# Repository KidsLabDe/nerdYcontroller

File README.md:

# Innovative Lernplatine mit Raspberry Pi Pico für angehende Programmierer

Diese benutzerfreundliche Platine ist speziell darauf ausgelegt, einen Raspberry Pi Pico aufzunehmen, und bietet eine interaktive Plattform, um die Grundlagen der Programmierung und Elektronik spielerisch zu erlernen.

**Hauptmerkmale:**

- **Vielseitiger Raspberry Pi Pico-Sockel:** Im Herzen der Platine befindet sich ein dedizierter Sockel, der perfekt für den Raspberry Pi Pico geeignet ist. Dies ermöglicht eine einfache Integration und eine robuste Verbindung.

- **Farbenfrohe LED-Anzeige:** Ausgestattet mit vier leuchtenden LEDs in verschiedenen Farben, bietet unsere Platine eine visuelle Rückmeldung für Programmierprojekte. Diese LEDs können für eine Vielzahl von Projekten programmiert werden, von einfachen Blinkmustern bis hin zu komplexeren Sequenzen.

- **Integrierter Neigungssensor:** Mit dem eingebauten Neigungssensor können Nutzer Bewegung und Ausrichtung in ihre Projekte einbeziehen. Dieser Sensor eröffnet spannende Möglichkeiten für interaktive Spiele und Experimente.

- **Kompakter Lautsprecher:** Ein kleiner, aber leistungsstarker Lautsprecher ermöglicht es, akustische Elemente in Projekte zu integrieren. Von einfachen Tonsignalen bis hin zu komplexen Melodien können die Nutzer ihre Kreativität voll ausleben.

- **Touch-Sensoren:** Die Platine verfügt über empfindliche Touch-Sensoren, die eine neue Dimension der Interaktivität bieten. Diese können für eine Vielzahl von Anwendungen genutzt werden, von Steuerelementen für Spiele bis hin zu kreativen musikalischen Experimenten.

- **Ideal für DIY-Gamecontroller:** Diese Platine ist nicht nur ein Lernwerkzeug, sondern auch eine Grundlage für den Bau eigener Gamecontroller. Nutzer können die vorhandenen Sensoren und Ausgänge verwenden, um einzigartige und individuelle Spieleerlebnisse zu schaffen.

**Anwendungsbereiche:**

Diese Platine ist ideal für Bildungseinrichtungen, Maker und alle, die einen praktischen und unterhaltsamen Einstieg in die Welt des Programmierens suchen. Sie bietet eine solide Grundlage für Projekte in den Bereichen Robotik, Spieleentwicklung und interaktive Kunst.

# Zusammenbau und erster Start

**Merke: Das Zusammenbauen ist nicht schwer - sie beim Löten zu brennen schmerzt dagegen sehr!** 

Daher immer auf die Finger obacht geben und den Lötkolben sicher ablegen!

## 1. Alles was du brauchst!

- Lötkolben, Lötzinn etc.
- 2 "Header" - die nutzen wir, um den Pico richtig auf der Platine zu platzieren. Im Notfall gehen auch 2 Büroklammern...
- einen [Raspberry Pico](https://www.berrybase.de/raspberry-pi-pico-rp2040-mikrocontroller-board) (oder [Pico W](https://www.berrybase.de/raspberry-pi-pico-w-rp2040-wlan-mikrocontroller-board))

## 2. Richtig platzieren

Lege den Pico auf die Platine. 

** Achtung - der USB-Stecker muss oben sein! **

Bitte achte auch darauf, dass der Pico nicht verschoben ist.

## 3. Let's Löt!

(Danke an Adafruit!)

- Lötkolben aufheizen
- Lötstelle mit Spitze berühren - am besten vor der Seite
- Etwas lötzinn zugeben
- 2-3 Sekunden warten!
- Jetzt etwas mehr Lötzinn von oben zugeben, es schmilzt an der Platine

Zuerst 2-3 Pins anlöten, zum Beispiel links oben und rechts unten - dann ist der Pico fest und du kannst die Header entfernen.

So sieht es aus, wenn alles fertig ist!

## 4. Anschließen und Software aufspielen!

- Stecke den Pico mit einem Micro-USB Kabel am Computer an.
- Wenn er neu ist, sollte er sofort wie ein USB-Stick auftauchen
- Wenn nicht, halte beim Anstecken die kleine weiße Taste "BOOTSEL" gedrückt.

So sieht das auf dem Mac aus:

(Bei Windows ein bisschen anders...)

Jetzt fehlt nur noch die "Firmware" - das ist die Basis-Software, damit der Pico Python sprechen kann: zusätzlich habe ich noch einen Beispiel-Python-Code drauf gemacht, dass es blinkt etc.

1. Lade diese Datei runter: https://github.com/KidsLabDe/PicoKrokoBirne/blob/main/firmware/PicoKrokoBirne.uf2
2. Kopiere sie auf die Pico im Finder / Explorer. Das geht meistens per Drag&Drop
3. Fertig!

Die PicoKrokoBirne sollte jetzt fröhlich bunt drauf losblinken!

## Anpassen und los programmieren!

Der Pico erscheint nun wiederum als USB-Laufwerk, diesmal heißt er "CIRCUITPY".
Dort findest du die Datei "code.py" - da drin passiert die Magie!

Als Editor empfehle ich dir den Mu-Editor: https://codewith.mu

Viel Spaß!

# Kontaktdaten

Du hast die Glühbirne als Visitenkarte bekommen? Sehr gut! 

Meine Kontaktdaten:

- Gregor Walter
- [gregor@kidslab.de](mailto:gregor@kidslab.de
- Telefon / WhatsApp: 0821-99951920 
- Mehr Infos über das gemeinnützige [KidsLab](https://kidslab.de) 

Ich freue mich auf deinen Anruf / eMail / Nachricht 🤖

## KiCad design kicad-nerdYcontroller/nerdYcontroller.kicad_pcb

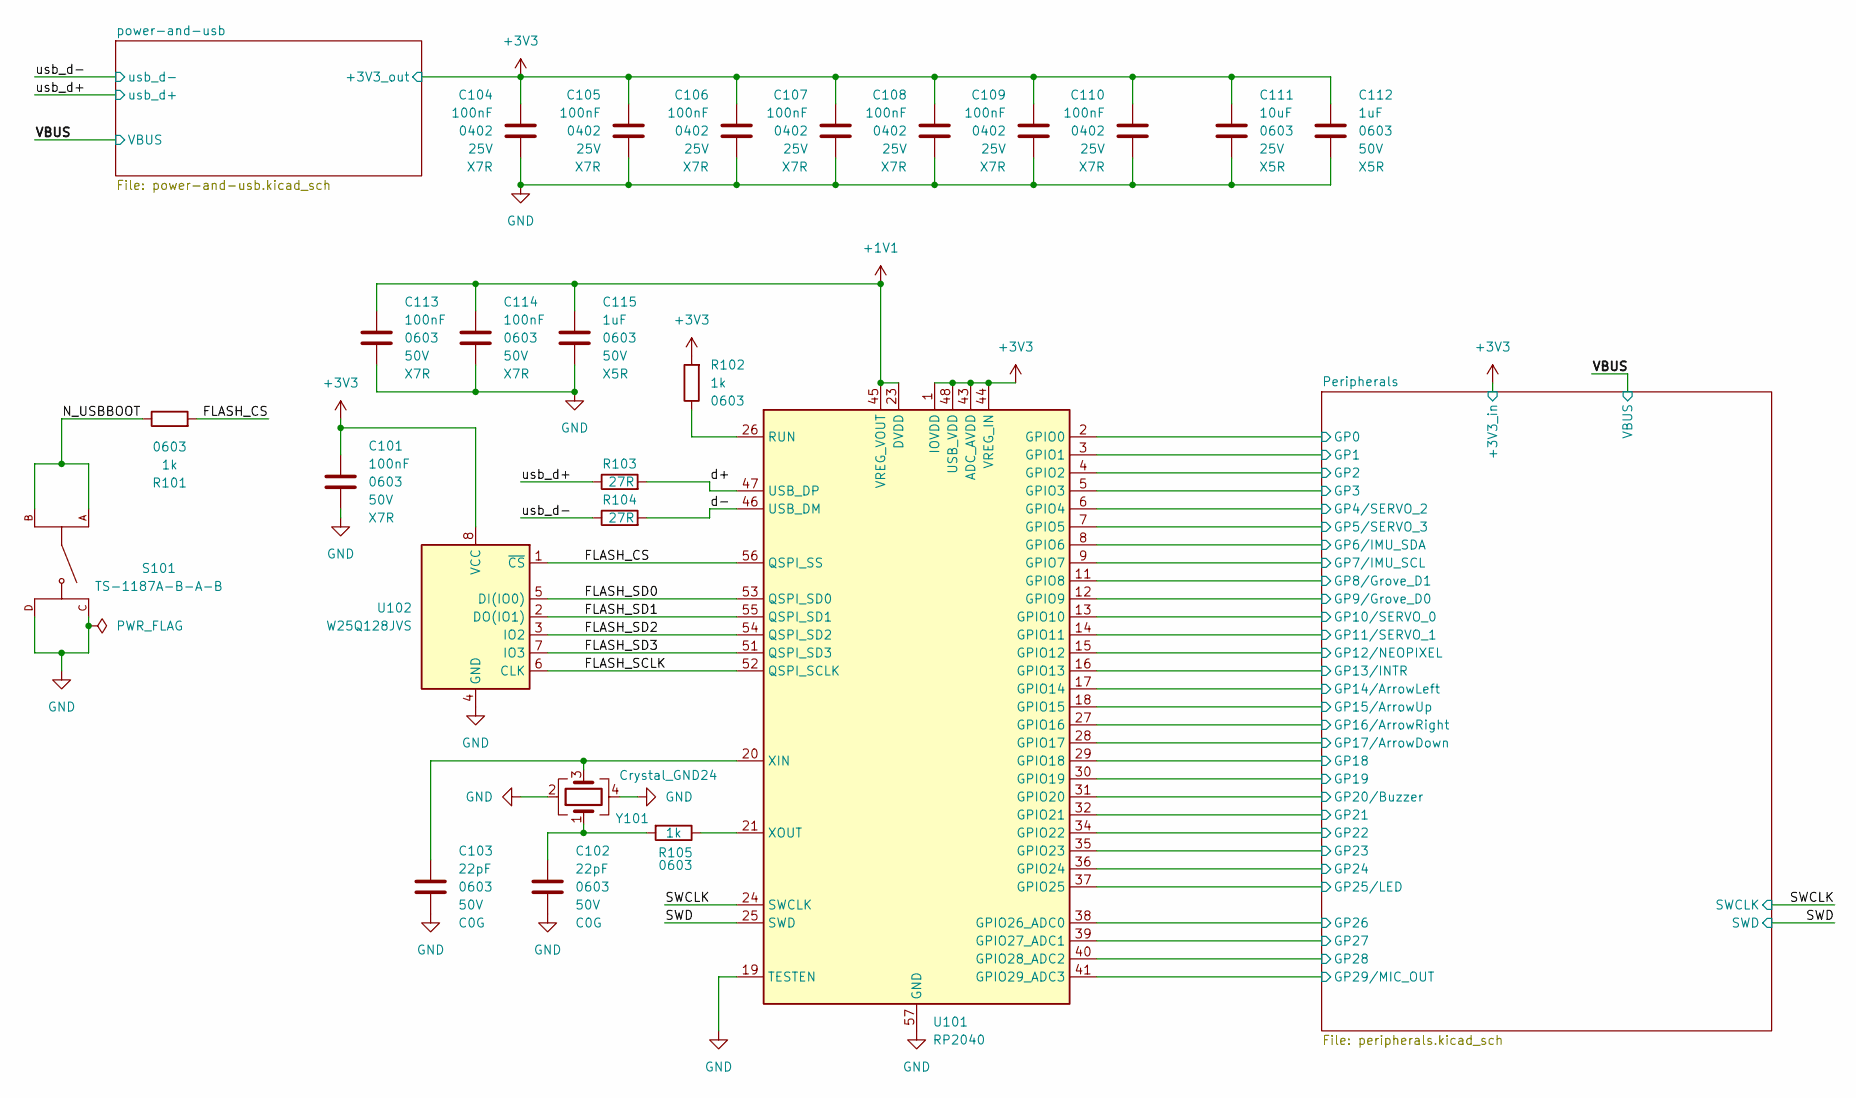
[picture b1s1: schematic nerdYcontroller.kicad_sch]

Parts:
C101, C113, C114: 100nF; C_0603_1608Metric; Voltage Rating 50V; LCSC Part # C14663
C102, C103: 22pF; C_0603_1608Metric; Voltage Rating 50V; LCSC Part # C1653
C104, C105, C106, C107, C108, C109, C110: 100nF; C_0402_1005Metric; Voltage Rating 25V; LCSC Part # C56392
C111: 10uF; C_0603_1608Metric; Voltage Rating 25V; LCSC Part # C96446
C112, C115: 1uF; C_0603_1608Metric; Voltage Rating 50V; LCSC Part # C15849
R101, R102, R105: 1k; R_0603_1608Metric; LCSC Part # C21190
R103, R104: 27R; R_0603_1608Metric; LCSC Part # C25190
S101: TS-1187A-B-A-B; SW_TS-1187A-B-A-B; LCSC Part # C318884
U101: RP2040; QFN-56-1EP_7x7mm_P0.4mm_EP3.2x3.2mm
U102: W25Q128JVS; SOIC-8_5.23x5.23mm_P1.27mm; LCSC Part # C97521
Y101: Crystal_GND24; Crystal_SMD_3225-4Pin_3.2x2.5mm; LCSC Part # C9002

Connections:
+1V1: C113.1, C114.1, C115.1, U101.23 (DVDD), U101.45 (VREG_VOUT), U101.50 (DVDD)
+3V3: C101.1, C104.2, C105.2, C106.2, C107.2, C108.2, C109.2, C110.2, C111.1, C112.1, R102.2, U101.1 (IOVDD), U101.10 (IOVDD), U101.22 (IOVDD), U101.33 (IOVDD), U101.42 (IOVDD), U101.43 (ADC_AVDD), U101.44 (VREG_IN), U101.48 (USB_VDD), U101.49 (IOVDD), U102.8 (VCC); also elsewhere on the board
/FLASH_CS: R101.2, U101.56 (QSPI_SS), U102.1 (~CS)
/FLASH_SCLK: U101.52 (QSPI_SCLK), U102.6 (CLK)
/FLASH_SD0: U101.53 (QSPI_SD0), U102.5 (DI(IO0))
/FLASH_SD1: U101.55 (QSPI_SD1), U102.2 (DO(IO1))
/FLASH_SD2: U101.54 (QSPI_SD2), U102.3 (IO2)
/FLASH_SD3: U101.51 (QSPI_SD3), U102.7 (IO3)
/N_USBBOOT: R101.1, S101.A, S101.B
/Peripherals/GP0: U101.2 (GPIO0); also elsewhere on the board
/Peripherals/GP1: U101.3 (GPIO1); also elsewhere on the board
/Peripherals/GP2: U101.4 (GPIO2); also elsewhere on the board
/Peripherals/GP3: U101.5 (GPIO3); also elsewhere on the board
/Peripherals/GP4/SERVO_2: U101.6 (GPIO4); also elsewhere on the board
/Peripherals/GP5/SERVO_3: U101.7 (GPIO5); also elsewhere on the board
/Peripherals/GP6/IMU_SDA: U101.8 (GPIO6); also elsewhere on the board
/Peripherals/GP7/IMU_SCL: U101.9 (GPIO7); also elsewhere on the board
/Peripherals/GP8/Grove_D1: U101.11 (GPIO8); also elsewhere on the board
/Peripherals/GP9/Grove_D0: U101.12 (GPIO9); also elsewhere on the board
/Peripherals/GP10/SERVO_0: U101.13 (GPIO10); also elsewhere on the board
/Peripherals/GP11/SERVO_1: U101.14 (GPIO11); also elsewhere on the board
/Peripherals/GP12/NEOPIXEL: U101.15 (GPIO12); also elsewhere on the board
/Peripherals/GP13/INTR: U101.16 (GPIO13); also elsewhere on the board
/Peripherals/GP14/ArrowLeft: U101.17 (GPIO14); also elsewhere on the board
/Peripherals/GP15/ArrowUp: U101.18 (GPIO15); also elsewhere on the board
/Peripherals/GP16/ArrowRight: U101.27 (GPIO16); also elsewhere on the board
/Peripherals/GP17/ArrowDown: U101.28 (GPIO17); also elsewhere on the board
/Peripherals/GP18: U101.29 (GPIO18); also elsewhere on the board
/Peripherals/GP19: U101.30 (GPIO19); also elsewhere on the board
/Peripherals/GP20/Buzzer: U101.31 (GPIO20); also elsewhere on the board
/Peripherals/GP21: U101.32 (GPIO21); also elsewhere on the board
/Peripherals/GP22: U101.34 (GPIO22); also elsewhere on the board
/Peripherals/GP23: U101.35 (GPIO23); also elsewhere on the board
/Peripherals/GP24: U101.36 (GPIO24); also elsewhere on the board
/Peripherals/GP25/LED: U101.37 (GPIO25); also elsewhere on the board
/Peripherals/GP26: U101.38 (GPIO26_ADC0); also elsewhere on the board
/Peripherals/GP27: U101.39 (GPIO27_ADC1); also elsewhere on the board
/Peripherals/GP28: U101.40 (GPIO28_ADC2); also elsewhere on the board
/Peripherals/GP29/MIC_OUT: U101.41 (GPIO29_ADC3); also elsewhere on the board
/SWCLK: U101.24 (SWCLK); also elsewhere on the board
/SWD: U101.25 (SWD); also elsewhere on the board
/d+: R103.2, U101.47 (USB_DP)
/d-: R104.2, U101.46 (USB_DM)
/usb_d+: R103.1; also elsewhere on the board
/usb_d-: R104.1; also elsewhere on the board
GND: C101.2, C102.2, C103.2, C104.1, C105.1, C106.1, C107.1, C108.1, C109.1, C110.1, C111.2, C112.2, C113.2, C114.2, C115.2, S101.C, S101.D, U101.19 (TESTEN), U101.57 (GND), U102.4 (GND), Y101.2, Y101.4; also elsewhere on the board
unnamed: C102.1, R105.2, Y101.1
unnamed: R102.1, U101.26 (RUN)
unnamed: C103.1, U101.20 (XIN), Y101.3
unnamed: R105.1, U101.21 (XOUT)

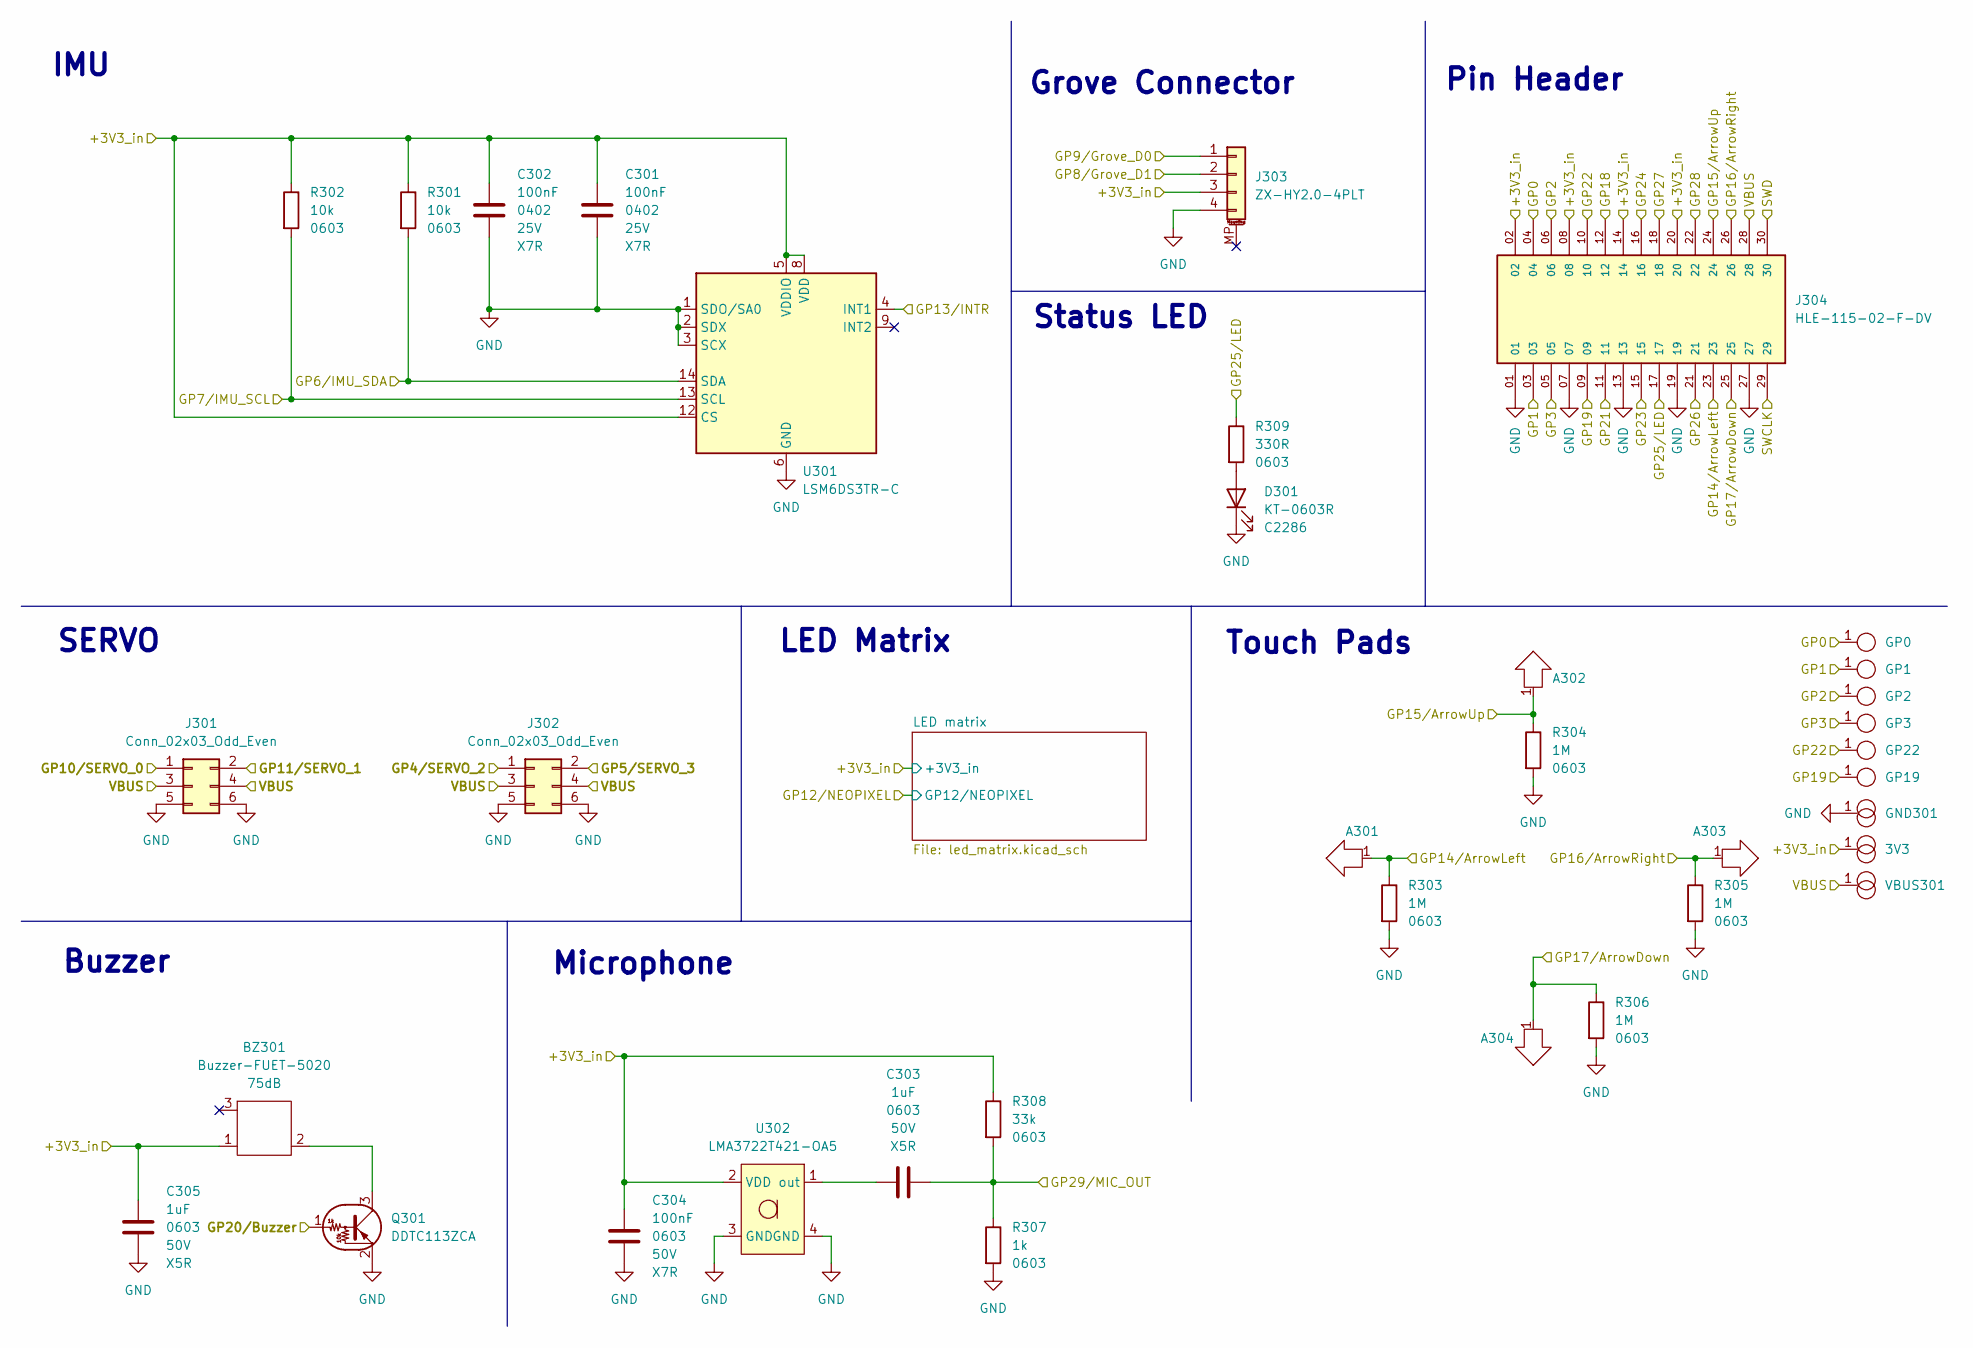
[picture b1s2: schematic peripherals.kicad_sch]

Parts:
3V3: kroko_doubleedge; DoubleEdge
A301, A302, A303, A304: arrow; Kroko_Arrow
BZ301: Buzzer-FUET-5020; FUET-5020; LCSC Part # C391029
C301, C302: 100nF; C_0402_1005Metric; Voltage Rating 25V; LCSC Part # C56392
C303, C305: 1uF; C_0603_1608Metric; Voltage Rating 50V; LCSC Part # C15849
C304: 100nF; C_0603_1608Metric; Voltage Rating 50V; LCSC Part # C14663
D301: KT-0603R; LED_0603_1608Metric; LCSC Part # C2286
GND301: kroko_doubleedge; DoubleEdge
GP0, GP1, GP2, GP3, GP19, GP22: kroko_edge; Edgeconnector
J301, J302: Conn_02x03_Odd_Even; PinHeader_2x03_P2.54mm_Vertical_SMD; LCSC Part # C192301
J303: ZX-HY2.0-4PLT; LCSC Part # C7429562
J304: HLE-115-02-F-DV; SAMTEC_HLE-115-02-F-DV
Q301: DDTC113ZCA; SOT-23; LCSC Part # C151437
R301, R302: 10k; R_0603_1608Metric; LCSC Part # C25804
R303, R304, R305, R306: 1M; R_0603_1608Metric; LCSC Part # C105578
R307: 1k; R_0603_1608Metric; LCSC Part # C21190
R308: 33k; R_0603_1608Metric; LCSC Part # C25593
R309: 330R; R_0603_1608Metric; LCSC Part # C22104
U301: LSM6DS3TR-C; LGA-14_3x2.5mm_P0.5mm_LayoutBorder3x4y; LCSC Part # C967633
U302: LMA3722T421-OA5; LCSC Part # C5373233
VBUS301: kroko_doubleedge; DoubleEdge

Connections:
+3V3: 3V3.1, BZ301.1 (+), C301.2, C302.2, C304.1, C305.1, J303.3, J304.02, J304.08, J304.14, J304.20, R301.1, R302.1, R308.1, U301.5 (VDDIO), U301.8 (VDD), U301.12 (CS), U302.2 (VDD); also elsewhere on the board
/Peripherals/GP0: GP0.1, J304.04; also elsewhere on the board
/Peripherals/GP1: GP1.1, J304.03; also elsewhere on the board
/Peripherals/GP2: GP2.1, J304.06; also elsewhere on the board
/Peripherals/GP3: GP3.1, J304.05; also elsewhere on the board
/Peripherals/GP4/SERVO_2: J302.1; also elsewhere on the board
/Peripherals/GP5/SERVO_3: J302.2; also elsewhere on the board
/Peripherals/GP6/IMU_SDA: R301.2, U301.14 (SDA); also elsewhere on the board
/Peripherals/GP7/IMU_SCL: R302.2, U301.13 (SCL); also elsewhere on the board
/Peripherals/GP8/Grove_D1: J303.2; also elsewhere on the board
/Peripherals/GP9/Grove_D0: J303.1; also elsewhere on the board
/Peripherals/GP10/SERVO_0: J301.1; also elsewhere on the board
/Peripherals/GP11/SERVO_1: J301.2; also elsewhere on the board
/Peripherals/GP13/INTR: U301.4 (INT1); also elsewhere on the board
/Peripherals/GP14/ArrowLeft: A301.1, J304.23, R303.1; also elsewhere on the board
/Peripherals/GP15/ArrowUp: A302.1, J304.24, R304.1; also elsewhere on the board
/Peripherals/GP16/ArrowRight: A303.1, J304.26, R305.1; also elsewhere on the board
/Peripherals/GP17/ArrowDown: A304.1, J304.25, R306.1; also elsewhere on the board
/Peripherals/GP18: J304.12; also elsewhere on the board
/Peripherals/GP19: GP19.1, J304.09; also elsewhere on the board
/Peripherals/GP20/Buzzer: Q301.1 (B); also elsewhere on the board
/Peripherals/GP21: J304.11; also elsewhere on the board
/Peripherals/GP22: GP22.1, J304.10; also elsewhere on the board
/Peripherals/GP23: J304.15; also elsewhere on the board
/Peripherals/GP24: J304.16; also elsewhere on the board
/Peripherals/GP25/LED: J304.17, R309.1; also elsewhere on the board
/Peripherals/GP26: J304.21; also elsewhere on the board
/Peripherals/GP27: J304.18; also elsewhere on the board
/Peripherals/GP28: J304.22; also elsewhere on the board
/Peripherals/GP29/MIC_OUT: C303.2, R307.1, R308.2; also elsewhere on the board
/SWCLK: J304.29; also elsewhere on the board
/SWD: J304.30; also elsewhere on the board
/VBUS: J301.3, J301.4, J302.3, J302.4, J304.28, VBUS301.1; also elsewhere on the board
GND: C301.1, C302.1, C304.2, C305.2, D301.1 (K), GND301.1, J301.5, J301.6, J302.5, J302.6, J303.4, J304.01, J304.07, J304.13, J304.19, J304.27, Q301.2 (E), R303.2, R304.2, R305.2, R306.2, R307.2, U301.1 (SDO/SA0), U301.2 (SDX), U301.3 (SCX), U301.6 (GND), U301.7 (GND), U302.3 (GND), U302.4 (GND); also elsewhere on the board
unnamed: BZ301.2 (-), Q301.3 (C)
unnamed: D301.2 (A), R309.2
unnamed: C303.1, U302.1 (out)

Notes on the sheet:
Pin Header
Buzzer
Grove Connector
SERVO
LED Matrix
Microphone
Status LED
IMU
Touch Pads

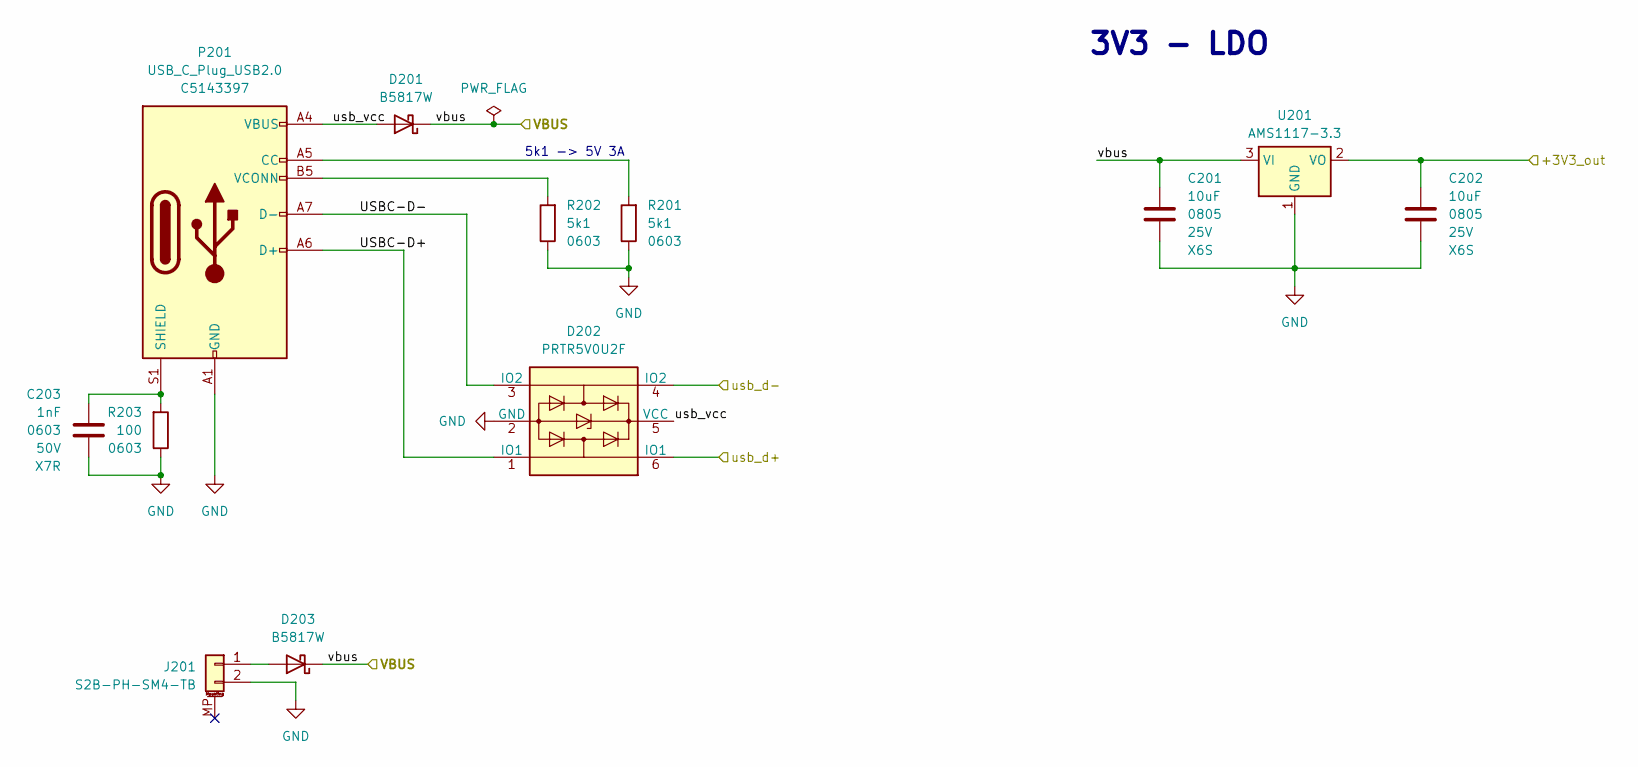
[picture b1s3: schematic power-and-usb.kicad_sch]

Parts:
C201, C202: 10uF; C_0805_2012Metric; Voltage Rating 25V; LCSC Part # C710989
C203: 1nF; C_0603_1608Metric; Voltage Rating 50V; LCSC Part # C1588
D201, D203: B5817W; D_SOD-123; LCSC Part # C2909923
D202: PRTR5V0U2F; WSON-6_1.5x1.5mm_P0.5mm; LCSC Part # C2937001
J201: S2B-PH-SM4-TB; JST_PH_S2B-PH-SM4-TB_1x02-1MP_P2.00mm_Horizontal; LCSC Part # C295747
P201: USB_C_Plug_USB2.0; USB_C_Receptacle_GCT_USB4110; LCSC Part # C5143397
R201, R202: 5k1; R_0603_1608Metric; LCSC Part # C23186
R203: 100; R_0603_1608Metric; LCSC Part # C22775
U201: AMS1117-3.3; SOT-223-3_TabPin2; LCSC Part # C6186

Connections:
+3V3: C202.1, U201.2 (VO); also elsewhere on the board
/VBUS: C201.1, D201.1 (K), D203.1 (K), U201.3 (VI); also elsewhere on the board
/power-and-usb/USBC-D+: D202.1 (IO1), P201.A6 (D+)
/power-and-usb/USBC-D-: D202.3 (IO2), P201.A7 (D-)
/power-and-usb/usb_vcc: D201.2 (A), D202.5 (VCC), P201.A4 (VBUS), P201.A9 (VBUS), P201.B4 (VBUS), P201.B9 (VBUS)
/usb_d+: D202.6 (IO1); also elsewhere on the board
/usb_d-: D202.4 (IO2); also elsewhere on the board
GND: C201.2, C202.2, C203.2, D202.2 (GND), J201.2, P201.A1 (GND), P201.A12 (GND), P201.B1 (GND), P201.B12 (GND), R201.1, R202.1, R203.1, U201.1 (GND); also elsewhere on the board
unnamed: D203.2 (A), J201.1
unnamed: P201.A5 (CC), R201.2
unnamed: C203.1, P201.S1 (SHIELD), R203.2
unnamed: P201.B5 (VCONN), R202.2

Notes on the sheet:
5k1 -> 5V 3A
3V3 - LDO

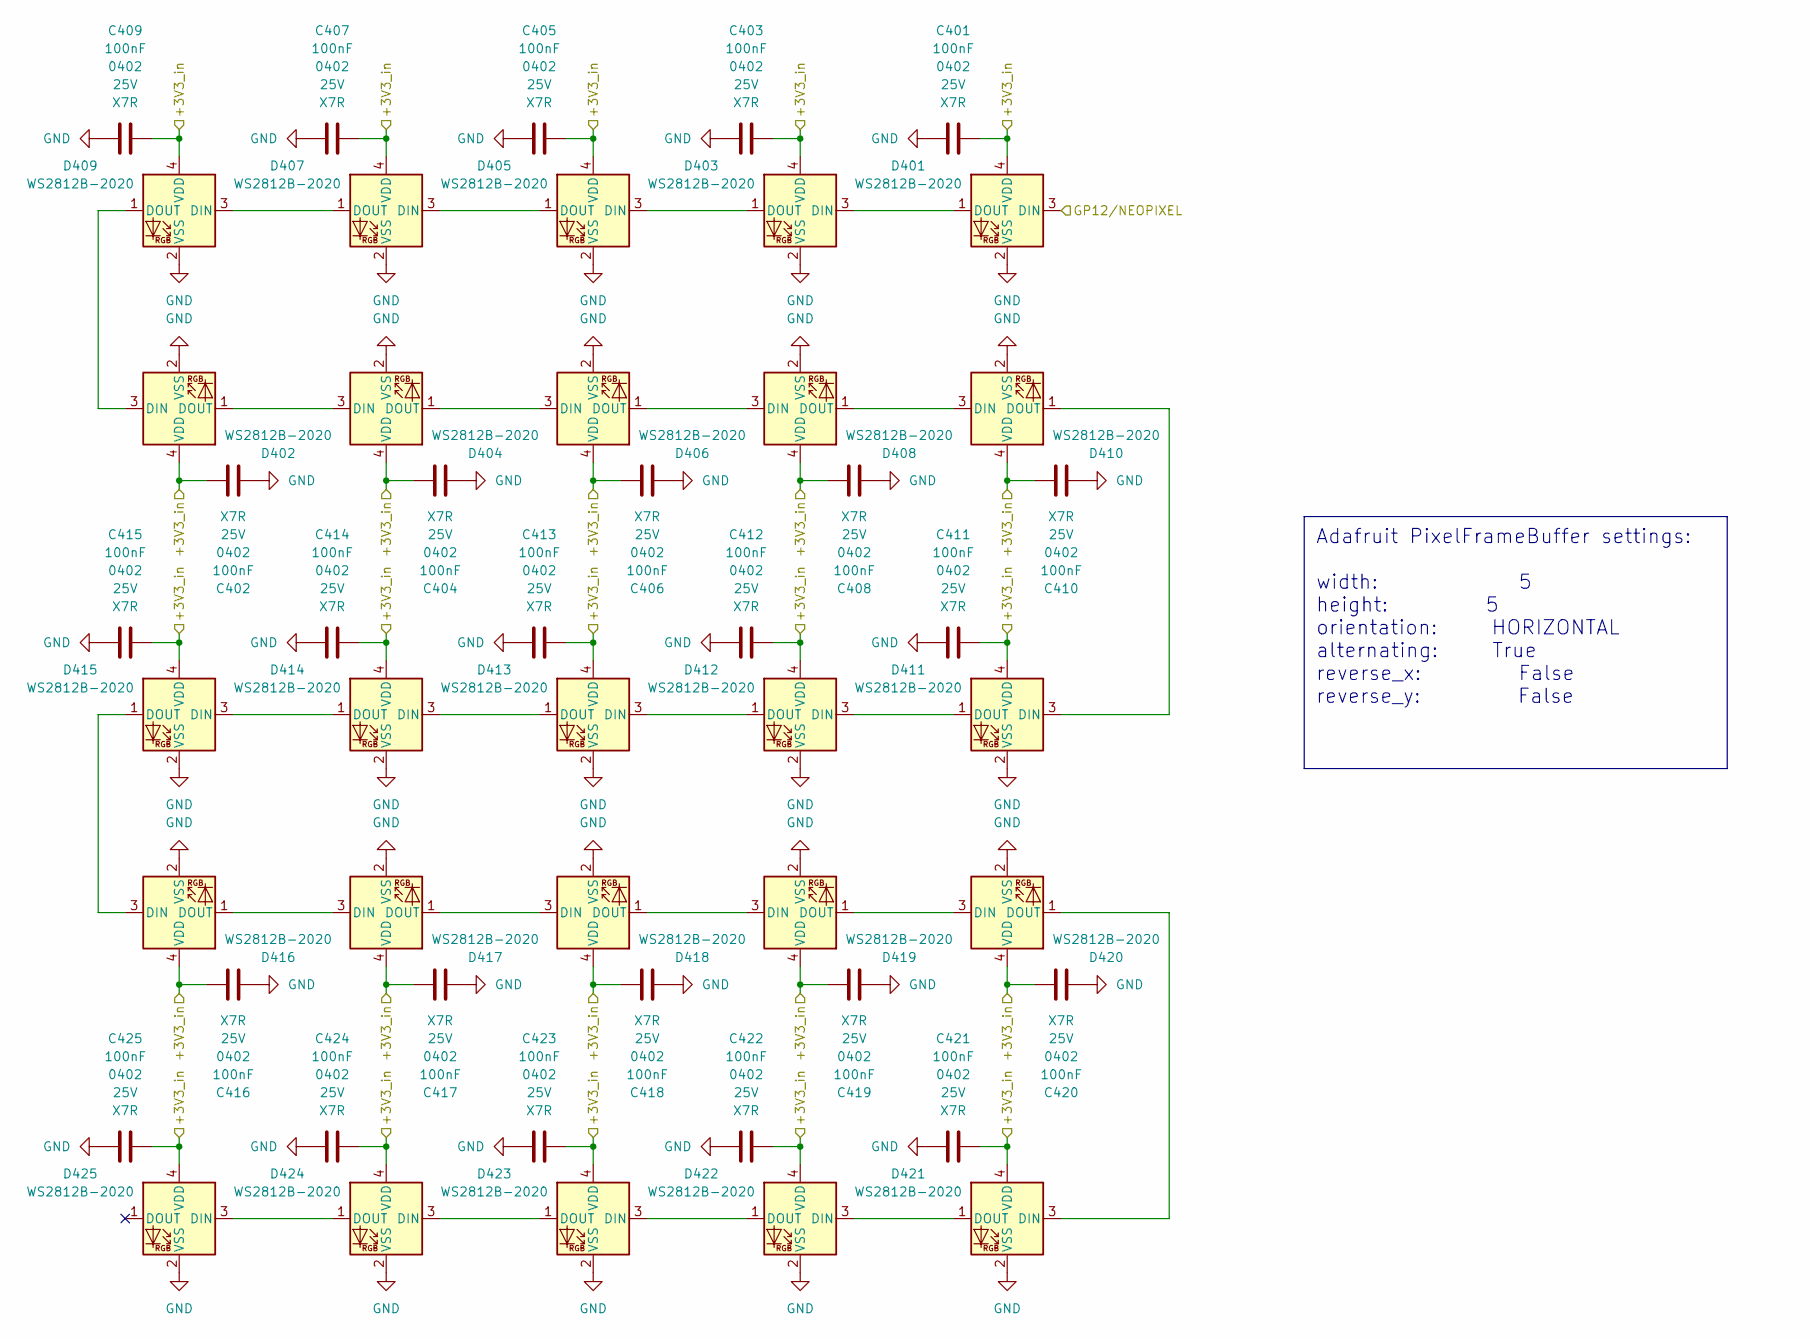
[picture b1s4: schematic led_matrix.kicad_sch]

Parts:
C401, C402, C403, C404, C405, C406, C407, C408, C409, C410, C411, C412, C413, C414, C415, C416, C417, C418, C419, C420, C421, C422, C423, C424, C425: 100nF; C_0402_1005Metric; Voltage Rating 25V; LCSC Part # C56392
D401, D402, D403, D404, D405, D406, D407, D408, D409, D410, D411, D412, D413, D414, D415, D416, D417, D418, D419, D420, D421, D422, D423, D424, D425: WS2812B-2020; LED_WS2812B-2020_PLCC4_2.0x2.0mm; LCSC Part # C965555

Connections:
+3V3: C401.1, C402.1, C403.1, C404.1, C405.1, C406.1, C407.1, C408.1, C409.1, C410.1, C411.1, C412.1, C413.1, C414.1, C415.1, C416.1, C417.1, C418.1, C419.1, C420.1, C421.1, C422.1, C423.1, C424.1, C425.1, D401.4 (VDD), D402.4 (VDD), D403.4 (VDD), D404.4 (VDD), D405.4 (VDD), D406.4 (VDD), D407.4 (VDD), D408.4 (VDD), D409.4 (VDD), D410.4 (VDD), D411.4 (VDD), D412.4 (VDD), D413.4 (VDD), D414.4 (VDD), D415.4 (VDD), D416.4 (VDD), D417.4 (VDD), D418.4 (VDD), D419.4 (VDD), D420.4 (VDD), D421.4 (VDD), D422.4 (VDD), D423.4 (VDD), D424.4 (VDD), D425.4 (VDD); also elsewhere on the board
/Peripherals/GP12/NEOPIXEL: D401.3 (DIN); also elsewhere on the board
GND: C401.2, C402.2, C403.2, C404.2, C405.2, C406.2, C407.2, C408.2, C409.2, C410.2, C411.2, C412.2, C413.2, C414.2, C415.2, C416.2, C417.2, C418.2, C419.2, C420.2, C421.2, C422.2, C423.2, C424.2, C425.2, D401.2 (VSS), D402.2 (VSS), D403.2 (VSS), D404.2 (VSS), D405.2 (VSS), D406.2 (VSS), D407.2 (VSS), D408.2 (VSS), D409.2 (VSS), D410.2 (VSS), D411.2 (VSS), D412.2 (VSS), D413.2 (VSS), D414.2 (VSS), D415.2 (VSS), D416.2 (VSS), D417.2 (VSS), D418.2 (VSS), D419.2 (VSS), D420.2 (VSS), D421.2 (VSS), D422.2 (VSS), D423.2 (VSS), D424.2 (VSS), D425.2 (VSS); also elsewhere on the board
unnamed: D401.1 (DOUT), D403.3 (DIN)
unnamed: D402.3 (DIN), D409.1 (DOUT)
unnamed: D402.1 (DOUT), D404.3 (DIN)
unnamed: D403.1 (DOUT), D405.3 (DIN)
unnamed: D404.1 (DOUT), D406.3 (DIN)
unnamed: D405.1 (DOUT), D407.3 (DIN)
unnamed: D406.1 (DOUT), D408.3 (DIN)
unnamed: D407.1 (DOUT), D409.3 (DIN)
unnamed: D408.1 (DOUT), D410.3 (DIN)
unnamed: D410.1 (DOUT), D411.3 (DIN)
unnamed: D411.1 (DOUT), D412.3 (DIN)
unnamed: D412.1 (DOUT), D413.3 (DIN)
unnamed: D413.1 (DOUT), D414.3 (DIN)
unnamed: D414.1 (DOUT), D415.3 (DIN)
unnamed: D415.1 (DOUT), D416.3 (DIN)
unnamed: D416.1 (DOUT), D417.3 (DIN)
unnamed: D417.1 (DOUT), D418.3 (DIN)
unnamed: D418.1 (DOUT), D419.3 (DIN)
unnamed: D419.1 (DOUT), D420.3 (DIN)
unnamed: D420.1 (DOUT), D421.3 (DIN)
unnamed: D421.1 (DOUT), D422.3 (DIN)
unnamed: D422.1 (DOUT), D423.3 (DIN)
unnamed: D423.1 (DOUT), D424.3 (DIN)
unnamed: D424.1 (DOUT), D425.3 (DIN)

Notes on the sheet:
Adafruit PixelFrameBuffer settings: width: 5 height: 5 orientation: HORIZONTAL alternating: True reverse_x: False reverse_y: False

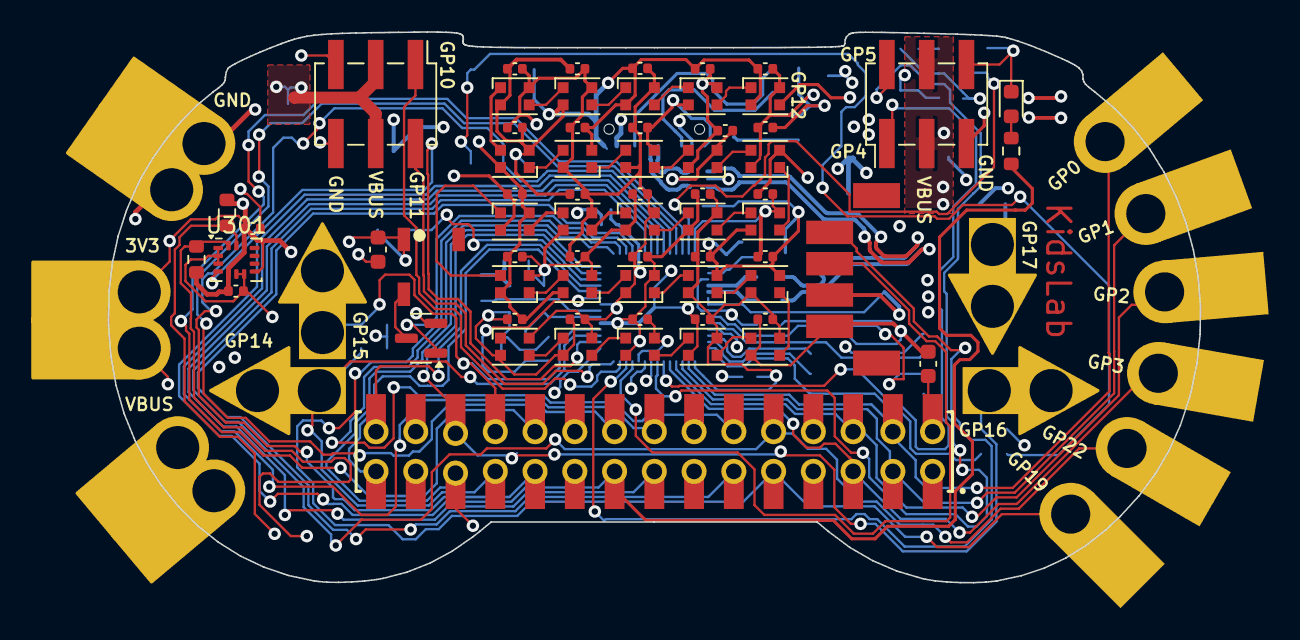
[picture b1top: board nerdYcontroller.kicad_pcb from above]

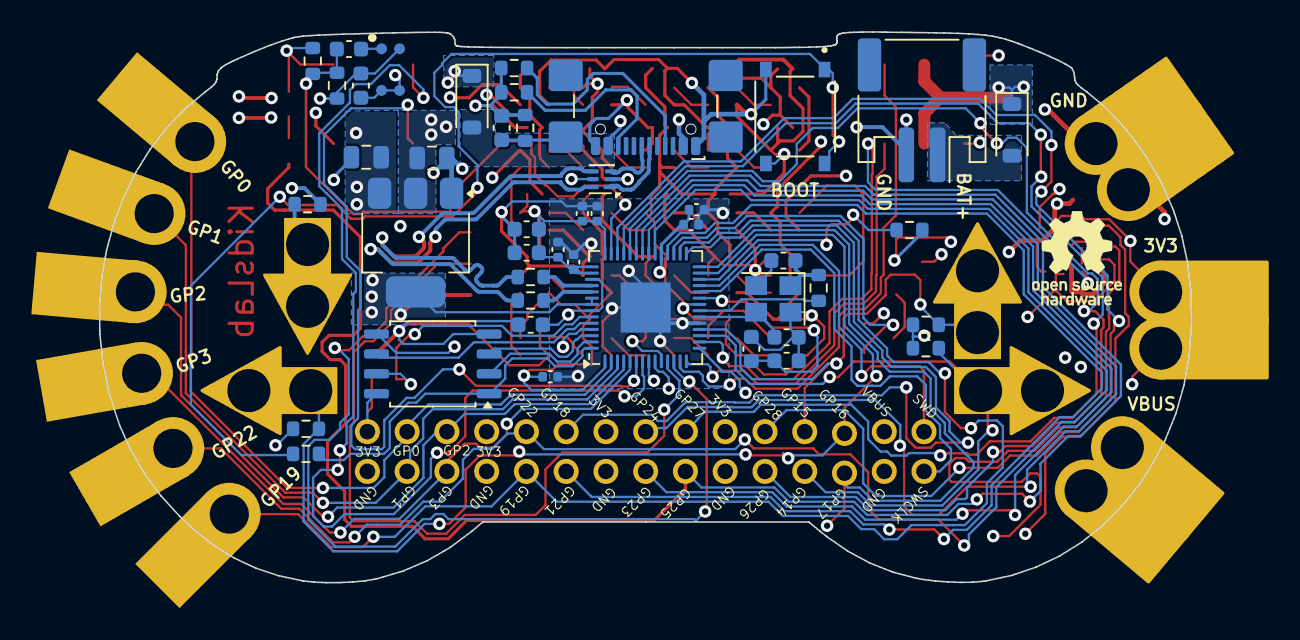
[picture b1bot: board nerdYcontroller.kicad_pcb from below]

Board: 4 copper layers, 69.8 x 35.2 mm, 123 parts (44 on the bottom side), 85 nets.

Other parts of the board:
outline: Gamecontroller Outline

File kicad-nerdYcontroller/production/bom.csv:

Designator,Footprint,Quantity,Value,LCSC Part #
BZ301,FUET-5020,1,Buzzer-FUET-5020,C391029
"C101, C113, C114, C304",0603,4,100nF,C14663
"C102, C103",0603,2,22pF,C1653
"C104, C105, C106, C107, C108, C109, C110, C301, C302, C401, C402, C403, C404, C405, C406, C407, C408, C409, C410, C411, C412, C413, C414, C415, C416, C417, C418, C419, C420, C421, C422, C423, C424, C425",0402,34,100nF,C56392
C111,0603,1,10uF,C96446
"C112, C115, C303, C305",0603,4,1uF,C15849
"C201, C202",0805,2,10uF,C710989
C203,0603,1,1nF,C1588
"D201, D203",D_SOD-123,2,B5817W,C2909923
D202,WSON-6_1.5x1.5mm_P0.5mm,1,PRTR5V0U2F,C2937001
D301,0603,1,KT-0603R,C2286
"D401, D402, D403, D404, D405, D406, D407, D408, D409, D410, D411, D412, D413, D414, D415, D416, D417, D418, D419, D420, D421, D422, D423, D424, D425",LED_WS2812B-2020_PLCC4_2.0x2.0mm,25,WS2812B-2020,C965555
J201,JST_PH_S2B-PH-SM4-TB_1x02-1MP_P2.00mm_Horizontal,1,S2B-PH-SM4-TB,C295747
"J301, J302",PinHeader_2x03_P2.54mm_Vertical_SMD,2,Conn_02x03_Odd_Even,C192301
J303,ZX-HY2.0-4PLT,1,ZX-HY2.0-4PLT,C7429562
J304,SAMTEC_HLE-115-02-F-DV,1,HLE-115-02-F-DV,
P201,USB_C_Receptacle_GCT_USB4110,1,USB_C_Plug_USB2.0,C5143397
Q301,SOT-23,1,DDTC113ZCA,C151437
"R101, R102, R105, R307",0603,4,1k,C21190
"R103, R104",0603,2,27R,C25190
"R201, R202",0603,2,5k1,C23186
R203,0603,1,100,C22775
"R301, R302",0603,2,10k,C25804
"R303, R304, R305, R306",0603,4,1M,C105578
R308,0603,1,33k,C25593
R309,0603,1,330R,C22104
S101,SW_TS-1187A-B-A-B,1,TS-1187A-B-A-B,C318884
U101,QFN-56-1EP_7x7mm_P0.4mm_EP3.2x3.2mm,1,RP2040,
U102,SOIC-8_5.23x5.23mm_P1.27mm,1,W25Q128JVS,C97521
U201,SOT-223-3_TabPin2,1,AMS1117-3.3,C6186
U301,LGA-14_3x2.5mm_P0.5mm_LayoutBorder3x4y,1,LSM6DS3TR-C,C967633
U302,LMA3722T421-OA5,1,LMA3722T421-OA5,C5373233
Y101,Crystal_SMD_3225-4Pin_3.2x2.5mm,1,Crystal_GND24,C9002
